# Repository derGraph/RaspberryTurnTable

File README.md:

# Raspberry Pi Zero LED + Motor HAT

This is a Motor HAT for Motor and LED PWM Control!

### Features
- PWM Light Control
- PWM Motor Control
- 16x1 Char LCD

Placed in a metal enclosure it makes a beautiful turntable.
The Raspberry Pi is powered with the Header but not the Voltage is not stabalized by this PCB.

## This Project is finished and will not be changed anymore

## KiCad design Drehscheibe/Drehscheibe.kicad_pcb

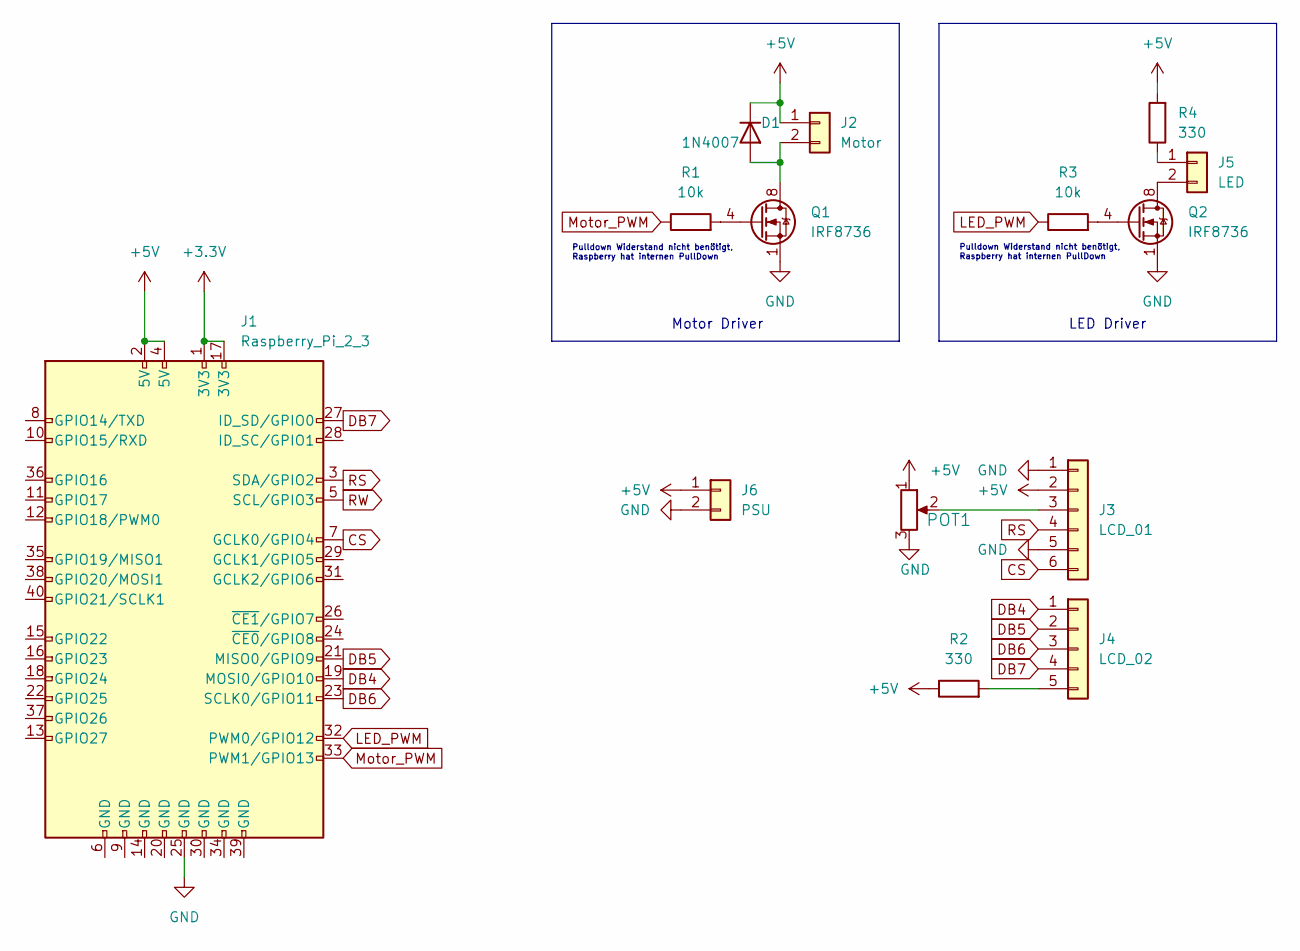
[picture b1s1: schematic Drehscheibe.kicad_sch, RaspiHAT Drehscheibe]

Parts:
D1: 1N4007; D_MicroMELF_Handsoldering
J1: Raspberry_Pi_2_3; PinSocket_2x20_P2.54mm_Vertical
J2: Motor; PinHeader_1x02_P2.54mm_Vertical
J3: LCD_01; PinHeader_1x06_P2.54mm_Vertical
J4: LCD_02; PinHeader_1x05_P2.54mm_Vertical
J5: LED; PinHeader_1x02_P2.54mm_Vertical
J6: PSU; PinHeader_1x02_P2.54mm_Vertical
POT1: 10k; Trimpot_3.8mmx3.6mm_TC33X-2-103E; MPN TC33X-2-103E; Digi-Key_PN TC33X-103ETR-ND
Q1, Q2: IRF8736; SO-8_3.9x4.9mm_P1.27mm
R1, R3: 10k; R_1210_3225Metric
R2, R4: 330; R_1210_3225Metric

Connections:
+3V3: J1.1 (3V3), J1.17 (3V3)
+5V: D1.1 (K), J1.2 (5V), J1.4 (5V), J2.1, J3.2, J6.1, POT1.1, R2.1, R4.2
CS: J1.7 (GCLK0/GPIO4), J3.6
DB4: J1.19 (MOSI0/GPIO10), J4.1
DB5: J1.21 (MISO0/GPIO9), J4.2
DB6: J1.23 (SCLK0/GPIO11), J4.3
DB7: J1.27 (ID_SD/GPIO0), J4.4
GND: J1.25 (GND), J3.1, J3.5, J6.2, POT1.3, Q1.1 (S), Q1.2 (S), Q1.3 (S), Q2.1 (S), Q2.2 (S), Q2.3 (S)
LED_PWM: J1.32 (PWM0/GPIO12), R3.1
Motor_PWM: J1.33 (PWM1/GPIO13), R1.1
unnamed: D1.2 (A), J2.2, Q1.5 (D), Q1.6 (D), Q1.7 (D), Q1.8 (D)
unnamed: J3.3, POT1.2
unnamed: J4.5, R2.2
unnamed: J5.1, R4.1
unnamed: J5.2, Q2.5 (D), Q2.6 (D), Q2.7 (D), Q2.8 (D)
unnamed: Q1.4 (G), R1.2
unnamed: Q2.4 (G), R3.2
RS: J1.3 (SDA/GPIO2), J3.4
RW: J1.5 (SCL/GPIO3)

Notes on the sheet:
LED Driver
Pulldown Widerstand nicht benötigt, Raspberry hat internen PullDown
Motor Driver

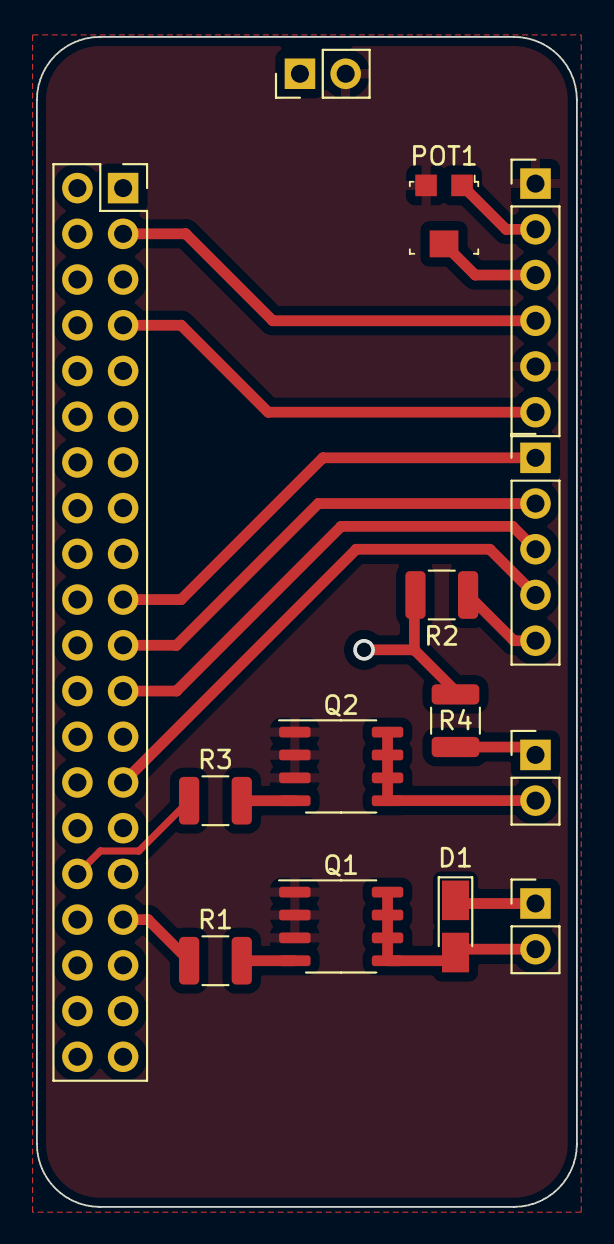
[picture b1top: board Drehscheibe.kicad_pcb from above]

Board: 2 copper layers, 30.0 x 65.0 mm, 14 parts (0 on the bottom side), 18 nets.

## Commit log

2023-04-29 new Version
